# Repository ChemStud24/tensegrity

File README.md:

README

This is the ROS package for controlling the tensegrity.  The tracking service and the simulator are in separate repos.  See https://sites.google.com/view/tensegrity-navigation/.  The "legacy" files are for testing with the old robot (Bluetooth), now deprecated.

Please use in conjunction with the ros branch of [tensgrity_perception](https://github.com/shiyoung77/tensegrity_perception/tree/ros)

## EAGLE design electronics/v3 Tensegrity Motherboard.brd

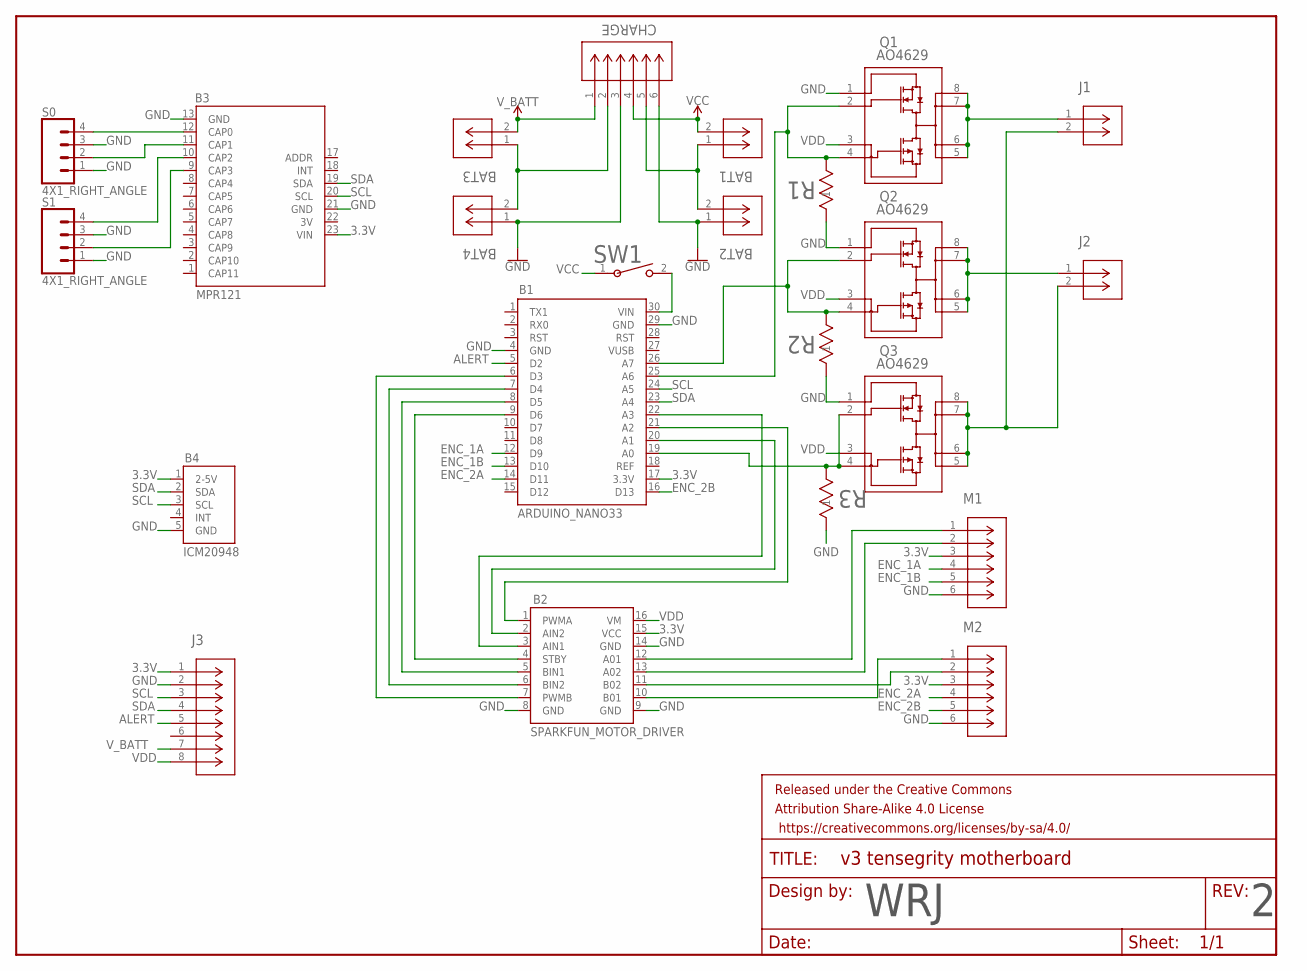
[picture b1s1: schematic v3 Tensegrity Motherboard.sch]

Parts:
B1: ARDUINO_NANO33; HDRVR30W64P1524X254_2X15_3810X1778X851B
B2: SPARKFUN_MOTOR_DRIVER; HDRVR16W64P1524X254_2X8_2032X2032X254B
B3: MPR121; HDRVR26W64P1524X254_2X13_3302X1905X851B
B4: ICM20948; HDRVR5W64P254_1X5_1270X254X851B
BAT1, BAT2, BAT3, BAT4: S2B-PH-K-S(LF)(SN); CONN_S2B-PH-K-S_JST
CHARGE: S6B-XH-A; CONN_S6B-XH-A_JST
FRAME1: FRAME-LETTER; CREATIVE_COMMONS
J1, J2: S2B-XH-A-1(LF)(SN); CONN_S2B-XH-A-1(LF)(SN)_JST
J3: PEC08SAAN; CONN_XXC08SAAN_SUL
M1, M2: BM06B-SRSS-TB(LF)(SN); CONN_BM06B-SRSS-TB_JST
Q1, Q2, Q3: AO4629; SO8(SOP-8L)_AOS
R1, R2, R3: RC0603FR-071KL; RC0603N_YAG
S0, S1: 4X1_RIGHT_ANGLE; HDRRA4W64P254_1X4_1016X254X278B
SW1: GPTS203212B; SW_GPTS203212B_CWI

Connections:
3.3V: B1.17 (3.3V), B2.15 (VCC), B3.23 (VIN), B4.1 (2-5V), J3.1, M1.3, M2.3
3V: B3.22 (3V)
ALERT: B1.5 (D2), J3.5
ENC_1A: B1.12 (D9), M1.4
ENC_1B: B1.13 (D10), M1.5
ENC_2A: B1.14 (D11), M2.4
ENC_2B: B1.16 (D13), M2.5
GND: B1.4 (GND), B1.29 (GND), B2.8 (GND), B2.9 (GND), B2.14 (GND), B3.13 (GND), B3.21 (GND), B4.5 (GND), BAT2.1, BAT4.1, CHARGE.3, CHARGE.6, J3.2, M1.6, M2.6, Q1.1, Q2.1, Q3.1, R1.1, R2.1, R3.1, S0.1, S0.3, S1.1, S1.3
unnamed: BAT1.1, BAT2.2, CHARGE.5
unnamed: BAT3.1, BAT4.2, CHARGE.2
unnamed: B1.6 (D3), B2.7 (PWMB)
unnamed: B1.7 (D4), B2.6 (BIN2)
unnamed: B1.8 (D5), B2.5 (BIN1)
unnamed: B1.9 (D6), B2.4 (STBY)
unnamed: B1.21 (A2), B2.1 (PWMA)
unnamed: B1.20 (A1), B2.2 (AIN2)
unnamed: B1.22 (A3), B2.3 (AIN1)
unnamed: B2.12 (A01), M1.1
unnamed: B2.13 (A02), M1.2
unnamed: B2.11 (B02), M2.2
unnamed: B2.10 (B01), M2.1
unnamed: B1.30 (VIN), SW1.2
unnamed: B3.12 (CAP0), S0.4
unnamed: B3.11 (CAP1), S0.2
unnamed: B3.10 (CAP2), S1.4
unnamed: B3.9 (CAP3), S1.2
unnamed: B1.26 (A7), Q2.2, Q2.4, R2.2
unnamed: B1.25 (A6), Q1.2, Q1.4, R1.2
unnamed: J1.2, J2.2, Q3.5, Q3.6, Q3.7, Q3.8
unnamed: B1.19 (A0), Q3.2, Q3.4, R3.2
unnamed: J2.1, Q2.5, Q2.6, Q2.7, Q2.8
unnamed: J1.1, Q1.5, Q1.6, Q1.7, Q1.8
SCL: B1.24 (A5), B3.20 (SCL), B4.3 (SCL), J3.3
SDA: B1.23 (A4), B3.19 (SDA), B4.2 (SDA), J3.4
VCC: BAT1.2, CHARGE.4, SW1.1
VDD: B2.16 (VM), J3.8, Q1.3, Q2.3, Q3.3
VUSB: B1.27 (VUSB)
V_BATT: BAT3.2, CHARGE.1, J3.7

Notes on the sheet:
WRJ

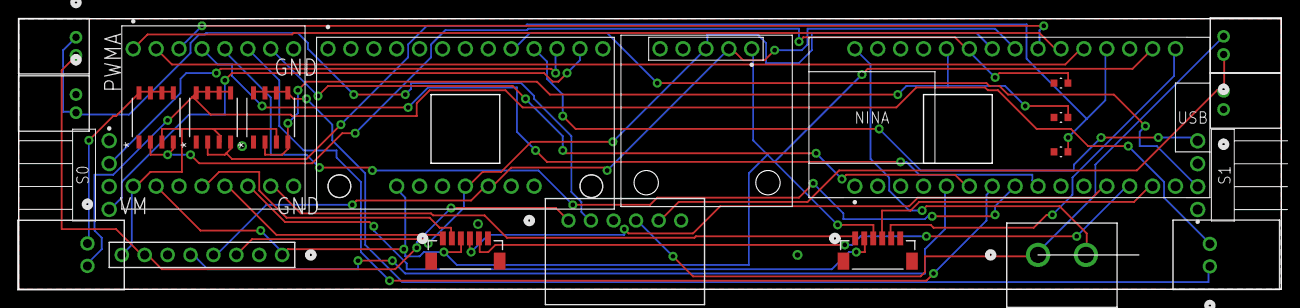
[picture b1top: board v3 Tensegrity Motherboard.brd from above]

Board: 2 copper layers, 140.0 x 30.0 mm, 24 parts (0 on the bottom side), 36 nets.

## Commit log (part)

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2025-01-14 README
2025-01-14 Planner has A* implemented A* not tested so bugs may exist
2025-01-14 small astar changes
2025-01-14 hardware testing
2025-01-15 bug fixes
2025-01-15 working with hardware (before state estimation)
2025-01-15 WIP testing with state estimation
2025-01-16 planning and tracking integrated - test
2025-01-16 successfully replanning
2025-01-17 new modeling results + heights
2025-01-20 Fixed "wave" (Obstacle informed) Heuristic
2025-01-21 drop experiments
2025-01-21 WiFi control - untested
2025-01-22 integrated WiFi and pose tracking - still testing
2025-01-22 manual control - untested
2025-01-28 getting WiFi up and running
2025-01-31 fixed heuristic hardcode
2025-01-31 fixed hardcodeing of heuristic
2025-01-31 new robot finally working
2025-02-01 electronics and Arduino code
2025-02-01 final experiments
2025-02-01 documentation
2025-02-25 encoder, accelerometer, and gyroscope
2025-02-25 gaits
2025-03-07 Fixed Wave heuristic bug
2025-03-24 rebutttal obstacle configurations
2025-03-27 Changed dist heuristic to only use 2d distance
2025-04-01 minor changes
2025-04-01 daemon threads for Keyboard Listener
2025-04-03 RL Policy Test
2025-04-03 RL wrapper
2025-04-03 test script
2025-04-04 flatten
2025-04-07 add policy_vel.py;
    the output of actor_5800000_osn.pth refers to actor velocity. policy_vel.py will transfer it to position command
2025-04-11 first draft at RL controller
2025-04-11 calibration
2025-04-14 successful integration test
2025-04-15 get action by policy after all action pos have been updated
2025-04-15 RL for new platform
2025-04-15 integration on new platform
2025-04-16 successfully rolled once
2025-04-16 changed speeds
2025-04-16 robosoft demo
2025-04-16 one rod test and separate file for RoboSoft demo
2025-04-17 successful demo
2025-04-17 sacrificial motherboard
2025-04-18 incorporate policy with positional control; use test_RL_policy.py to check; incorporate the new policy into legacy_run_tensegrity_RL.py;
    Note: The new policy need tracking point data (should be located in front of the robot and determined with the robot's initial pos). The function policy.reset_target_point() should be used to initial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
2025-04-18 avoid double using the reset_target_point()
2025-04-22 data logging
2025-04-30 Luca's manual fix
2025-04-30 fixed IMU bug
2025-05-07 preserve Will's laptop IP
2025-05-07 new sensors
2025-05-09 add a new positional control policy for task: tracking a target point; add 2 optional mode: use low pass filter or not; use determined action or not
2025-05-15 adapted changes wrt target point to run_tensegrity_RL.py for new robot platform
2025-05-15 ported changes to new platform
2025-05-16 1. mapping action_scale to the control range of active tendon; 2. use_low_pass_filter = False
2025-05-16 plot the recorded control data
2025-05-17 change fps to 8 Hz
2025-05-19 plotted vs. time (s) and added legend
2025-05-19 enable low-pass filter
2025-05-19 ctrl data recorder wrt each command loop
2025-05-27 fixed pointer bug
2025-05-27 gitignore
2025-05-27 fixed IMU pointer bug
2025-05-27 removed try...except from onpress
2025-05-27 fix a bug for low-pass filter
2025-05-27 fixed imu_id bug
2025-05-28 getting closer to fixing the disobedience bug
2025-05-31 outdoor closed-loop
2025-07-07 remove previously committed python bytecode
2025-07-07 anonymous site
2026-02-24 mppi
2026-02-26 Fixed perception packages
2026-02-26 Added encoder translation from raw encoder data to predicted length
2026-02-26 changed flip
2026-02-27 safety limit for mppi
2026-02-27 Charles' changes
2026-02-27 added gnn_simulator
2026-02-27 fix cable lengths limit error
2026-02-27 RA-L revisions
2026-02-27 change all expected input and output to mppi_planner to mm units
2026-02-27 change resolution
2026-02-27 fixed perception_utils problem
2026-02-27 Minor file path edits
2026-02-28 code running but mppi is making micro adjustments
2026-02-28 changed mppi params
2026-03-01 changed m/mm unit error
2026-03-01 Stop tracking calibration/ files
2026-03-02 sunday's changes
2026-03-02 added back calibration dir without xls
2026-03-02 changed symmetry reduction
2026-03-03 Monday Bug Fixes
2026-03-03 small fixes and tests
2026-03-04 Tuesday Changes
2026-03-04 update cable length safety sampling and mppi_planner min z shift
2026-03-04 mppi_planner now matches real world setup
2026-03-04 config hsv range change
2026-03-05 encoder information published
2026-03-06 new gnn_simulator
2026-03-07 fixed torch compile bug
2026-03-10 calibrated abra
2026-03-25 Fixed motor encoder information
2026-03-25 Added absolute encoder length parameter
2026-03-26 MARS
2026-04-03 new onboard code
2026-04-08 Test onboard code
2026-04-29 add dummy jit torch compile to mppi and make it persistent across trials
2026-05-11 started script for running with pump. modified encoders script, but that still needs work to address drift in encoders.
2026-05-11 started script for running witha pump.
2026-05-17 working gait for variable stiffness tendon and two mostly good videos
2026-05-27 syncing after variable stiffness video
2026-05-28 Fixed state estimation

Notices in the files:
parts and their libraries:
SparkFun-Aesthetics: Licensing: Creative Commons ShareAlike 4.0 International - https://creativecommons.org/licenses/by-sa/4.0
SparkFun-Aesthetics: Released under the Creative Commons Attribution Share-Alike 4.0 License
SparkFun-Aesthetics: https://creativecommons.org/licenses/by-sa/4.0
